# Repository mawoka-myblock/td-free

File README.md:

opencode -s ses_eeea170f0ffeTvjjMf0spo0cMp

# Td-Free

A free and open source device to measure the td value of your filaments.

Documentation: [API.md](API.md) describes the HTTP API, [FIRMWARE.md](FIRMWARE.md) explains how the firmware works.

The CAD is available in the [onshape workspace](https://cad.onshape.com/documents/e7ec65aec40b24c9a33c1902/w/dc90f86d4d08d2181a707cee/e/a86c6c8c0a4124509901ffce)
(licensed under [CC BY-SA 4.0](https://creativecommons.org/licenses/by-sa/4.0/)) and the print files can be downloaded from [Printables](https://www.printables.com/model/919380-td-free)

## Comparison to TD-1 by Ajax

| TD-Free                   | TD-1                                     |
| ------------------------- | ---------------------------------------- |
| **Small**                 | Slightly bigger                          |
| **Cheap**                 | More expensive                           |
| Measures td and color     | **Measures color and td**                |
| WiFi-enabled              | Only via usb and screen                  |
| **Open-Source Code**      | Closed source                            |
| **No license required**   | License needs to be purchased            |
| No integrations available | **Perfectly integrated into HueForge**   |
| **CAD available**         | CAD not available                        |
| only for checking samples | **monitor td of spool as it's printing** |

So, in summary, the Td-Free is **cheaper**, **open-source**, **smaller** and **wifi-enabled**.

## Buy one

**Explore [my online store](https://mawoka.eu/shop) where you can buy the PCB or a fully assembled Td-Free.**

## Make one

### Buy only the PCB

If you got the PCB, just print the parts provided at [Printables](https://www.printables.com/model/919380-td-free-an-open-source-alternative-to-the-td-1).
You have to use black filament for the specifc parts marked as such, but for the others, you can mix and match them! Let's get to the assembly:

1. Insert the LED module into the position in the case at the bottom. Press it down firmly.
2. Insert the two black pieces. The one with the channel first, so that the channel is open to the top. Make sure you see the yellow LED module through the hole in the channel!
3. Now, insert the second black piece with the rectangular cutout as well. Make sure again that the cutout is above the LED hole.
4. Slide the PCb with the USB-C connector in at an angle and make sure it's fully slid in.
5. Push the PCb into place and make sure it is really sitting flat. **Watch out for the LED cable to not get damaged!**
6. Put the lid on
7. Done! Measure your Td!

### From Scratch
Get the PCB from a manufacturer like JLCPCB, PCBway or whatever. Now, you'll also want to get the following components:
- `VEML7700` (TR or TT is only about the packaging, so choose the cheaper one)
- `WS2812B` (In the 5050 variant)
- `ESP32-C3 Supermini` ([Here from AliExpress](https://s.click.aliexpress.com/e/_DmNdnTB))
- `AOSS32334C`
- [This LED module](https://s.click.aliexpress.com/e/_DF3Gdpb) Get the Cold White version

Solder all your parts to the PCB. The LED module cables have to solderd from the bottom and should be around 45mm long.
Now, follow all the steps from above. For flashing, just follow the instructions to get Esp-rs working and run `cargo run --release`.

## Looking for the old README?
Click [here](https://github.com/mawoka-myblock/td-free/blob/v2.0.0/README.md).

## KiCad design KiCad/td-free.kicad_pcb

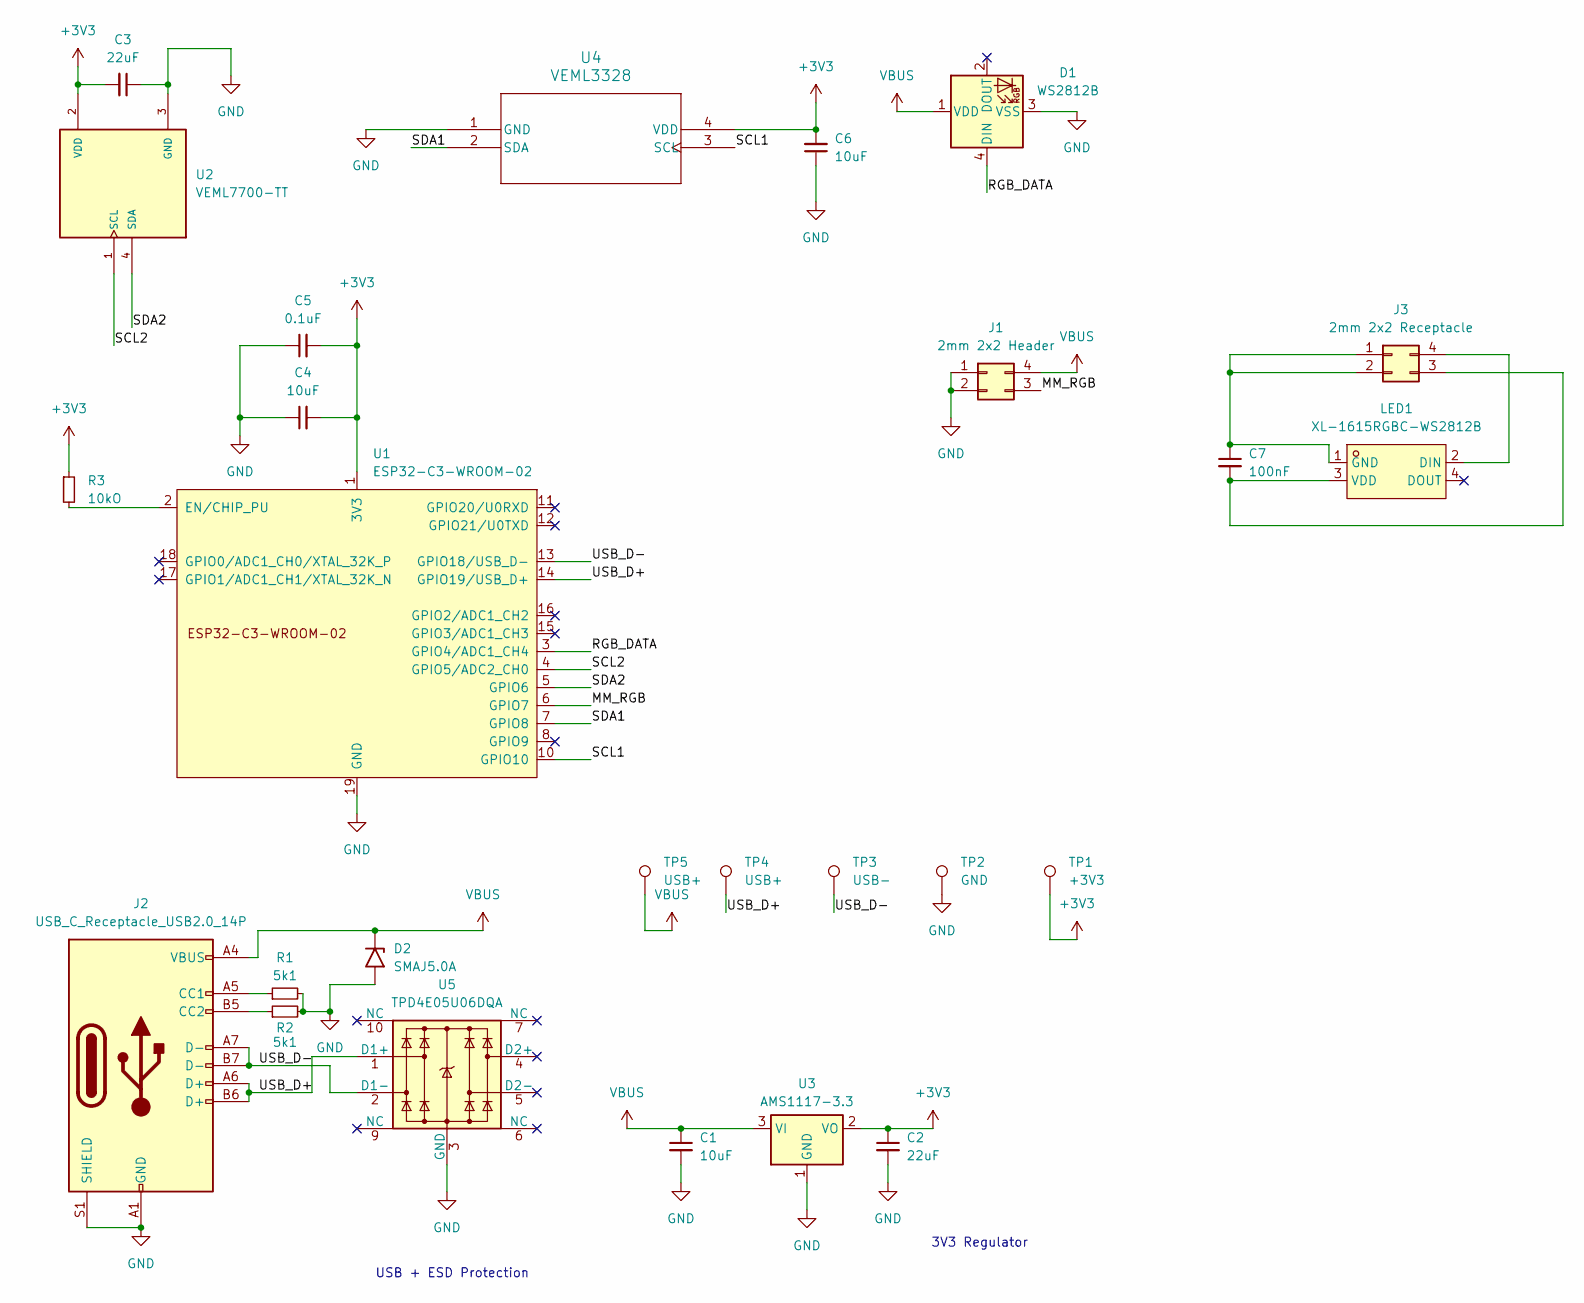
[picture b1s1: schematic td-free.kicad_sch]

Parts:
C1, C4, C6: 10uF; C_0805_2012Metric
C2, C3: 22uF; C_0805_2012Metric
C5: 0.1uF; C_0805_2012Metric
C7: 100nF; C_0805_2012Metric
D1: WS2812B; LED_WS2812B_PLCC4_5.0x5.0mm_P3.2mm
D2: SMAJ5.0A; D_SMA
J1: 2mm 2x2 Header; HDR-SMD_4P-P2.00-V-M-R2-C2-LS6.4-EH
J2: USB_C_Receptacle_USB2.0_14P; USB_C_Receptacle_GCT_USB4105-xx-A_16P_TopMnt_Horizontal
J3: 2mm 2x2 Receptacle; PinHeader_2x02_P2.00mm_Vertical_SMD
LED1: XL-1615RGBC-WS2812B; LED-SMD_4P-L1.6-W1.5_XL-1615RGBC-WS2812B-1; LCSC Part C5349954
R1, R2: 5k1; R_0805_2012Metric_Pad1.20x1.40mm_HandSolder
R3: 10kO; R_0805_2012Metric_Pad1.20x1.40mm_HandSolder
TP1: +3V3; TestPoint_Pad_D1.0mm
TP2: GND; TestPoint_Pad_D1.0mm
TP3: USB-; TestPoint_Pad_D1.0mm
TP4, TP5: USB+; TestPoint_Pad_D1.0mm
U1: ESP32-C3-WROOM-02
U2: VEML7700-TT; XDCR_VEML7700-TT; PARTREV 1.6
U3: AMS1117-3.3; SOT-223-3_TabPin2
U4: VEML3328; SMD_L3328_VIS
U5: TPD4E05U06DQA; USON-10_2.5x1.0mm_P0.5mm

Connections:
+3V3: C2.1, C3.2, C4.2, C5.2, C6.2, R3.1, TP1.1 (1_1), U1.1 (3V3), U2.2 (VDD), U3.2 (VO), U4.4 (VDD)
/MM_RGB: J1.3, U1.6 (GPIO7)
/RGB_DATA: D1.4 (DIN), U1.3 (GPIO4/ADC1_CH4)
/SCL1: U1.10 (GPIO10), U4.3 (SCL)
/SCL2: U1.4 (GPIO5/ADC2_CH0), U2.1 (SCL)
/SDA1: U1.7 (GPIO8), U4.2 (SDA)
/SDA2: U1.5 (GPIO6), U2.4 (SDA)
/USB_D+: J2.A6 (D+), J2.B6 (D+), TP4.1 (1_1), U1.14 (GPIO19/USB_D+), U5.1 (D1+)
/USB_D-: J2.A7 (D-), J2.B7 (D-), TP3.1 (1_1), U1.13 (GPIO18/USB_D-), U5.2 (D1-)
GND: C1.2, C2.2, C3.1, C4.1, C5.1, C6.1, D1.3 (VSS), D2.2 (A2), J1.1, J1.2, J2.A1 (GND), J2.A12 (GND), J2.B1 (GND), J2.B12 (GND), J2.S1 (SHIELD), R1.2, R2.2, TP2.1 (1_1), U1.9 (GND), U1.19 (GND), U2.3 (GND), U3.1 (GND), U4.1 (GND), U5.3 (GND), U5.8 (GND)
unnamed: J2.A5 (CC1), R1.1
unnamed: J2.B5 (CC2), R2.1
unnamed: C7.1, J3.1, J3.2, LED1.1 (GND)
unnamed: C7.2, J3.3, LED1.3 (VDD)
unnamed: J3.4, LED1.2 (DIN)
unnamed: R3.2, U1.2 (EN/CHIP_PU)
VBUS: C1.1, D1.1 (VDD), D2.1 (A1), J1.4, J2.A4 (VBUS), J2.A9 (VBUS), J2.B4 (VBUS), J2.B9 (VBUS), TP5.1 (1_1), U3.3 (VI)

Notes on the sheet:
3V3 Regulator
USB + ESD Protection

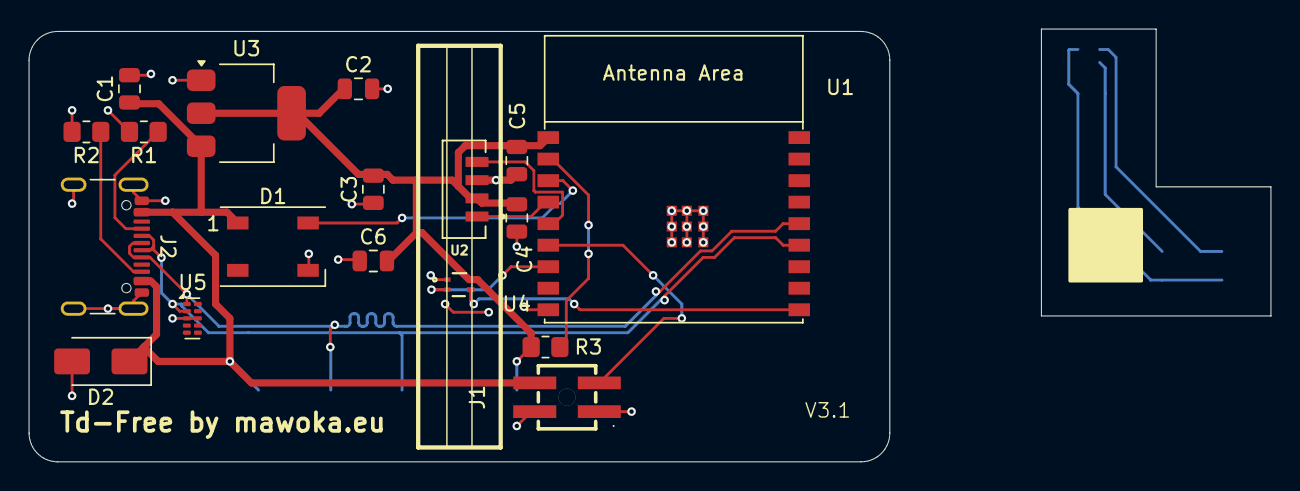
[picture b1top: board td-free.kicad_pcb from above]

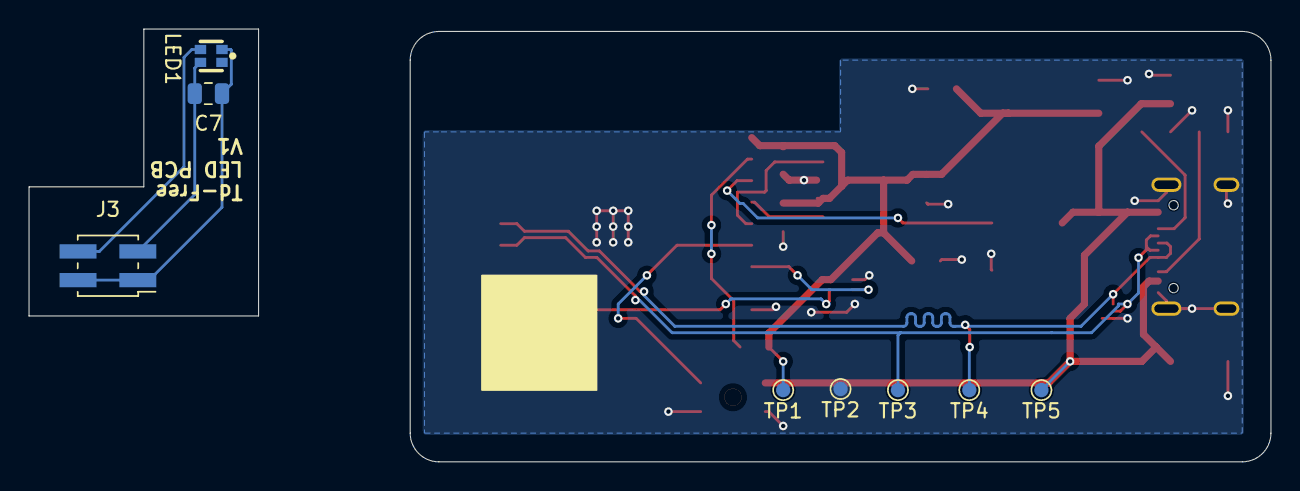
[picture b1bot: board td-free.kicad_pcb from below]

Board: 2 copper layers, 60.0 x 30.0 mm, 28 parts (8 on the bottom side), 17 nets.

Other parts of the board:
B1, B2: Board

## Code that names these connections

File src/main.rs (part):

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        LedcDriver::new(
            peripherals.ledc.channel1,
            light_timer_driver,
            peripherals.pins.gpio7,
        )
        .unwrap(),
    ));
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        LedType::new(peripherals.rmt.channel0, peripherals.pins.gpio21).unwrap(),
    ));
    let ws2812_new: ArcLed = Arc::new(Mutex::new(
        LedType::new(peripherals.rmt.channel1, peripherals.pins.gpio4).unwrap(),
    ));
    ws2812_old
        .lock()
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    let veml_res = esp_idf_svc::hal::task::block_on(initialize_veml(
        Pins {
            i2c: peripherals.i2c0,
            sda1: peripherals.pins.gpio6,
            scl1: peripherals.pins.gpio5,
            sda2: peripherals.pins.gpio8,
            scl2: peripherals.pins.gpio10,
        },
        ws2812_old.clone(),
        ws2812_new.clone(),
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    // --- Serial connection setup ---
    let mut serial_driver = UsbSerialDriver::new(
        peripherals.usb_serial,
        peripherals.pins.gpio18,
        peripherals.pins.gpio19,
        &UsbSerialConfig::new(),
    )
    .unwrap();
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
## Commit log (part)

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2024-06-21 :sparkles: Working version
2024-06-21 :sparkles: Update workflow
2024-06-21 :sparkles: Finalized README.md
2024-07-06 Link to different ESP32-C3
2024-07-16 :sparkles: Create aio build for CI to upload with single file to esp32
2024-07-16 :sparkles: Improved readme
2024-08-09 :bug: Fix prebuilt binary not working
2024-09-07 Update note for V2
2024-10-14 :sparkles: V3 with PCB
2024-10-26 :sparkles: Algorithm adjustments possible
2024-10-26 :sparkles: inital try at release automation
2024-10-26 :sparkles: CI Update 1
2024-10-26 :sparkles: CI Update 2
2024-10-26 :sparkles: CI Update 3
2024-10-26 :sparkles: CI Update 4
2024-10-26 :sparkles: CI Update 5
2024-10-26 :sparkles: CI Update 6
2024-10-26 :sparkles: CI Update 7
2024-10-26 Add V1.2 PCB without wrong condensator
2024-10-26 Add more specific note on parts for self-sourcing
2024-10-26 Optimize trace on PCB
2024-10-26 Fix typo in README
2024-11-06 Create LICENSE
2024-12-20 :sparkles: Allow comma digit input for algorithm page
2024-12-20 :bug: Pin rust toolchain for github action
2024-12-21 :bug: Fix build issues
2024-12-30 Init mdns
2025-01-16 :sparkles: Version injection on website
2025-01-31 :sparkles: Handlers split into separate file
2025-01-31 :sparkles: Improved error handling
2025-02-01 :wip: Progress
2025-02-01 :bug: Fix build script
2025-02-01 :wip: basic changes
2025-02-01 :wip: Edge-Http test
2025-02-01 :wip: Compiling but panicking
2025-02-02 :wip: Changes
2025-02-02 Make the WS thing run
2025-02-03 :wip: Basics working with edge-http
2025-02-03 :wip: Basics working formatted
2025-02-03 :sparkles: Better WebSocket now working
2025-02-03 :sparkles: Final refactoring finished
2025-02-04 :sparkles: Fix GitHub Actions Release Build
2025-02-04 :bug: CI fix
2025-02-04 Fix GitHub Actions build again
2025-02-08 :sparkles: Working serial connection
2025-02-10 :sparkles: Averaged reading progress
2025-02-10 :bug: Fix release build file
2025-02-13 Quick save
2025-02-23 :sparkles: Averaged data working
2025-02-23 :bug: Fix release workflow
2025-02-23 :bug: Add small delay on page load before connecting to websocket
2025-03-09 :sparkles: First Prototype for improved PCB
2025-03-09 :sparkles: Even better fallback handling
2025-03-09 :sparkles: Adjustable threshold
2025-03-09 :bug: Fix formatting in algorithm page
2025-03-15 :sparkles: First test with new PCB
2025-03-28 :sparkles: PCB Progress
2025-03-28 :sparkles: Further USB support progress
2025-03-29 :sparkles: Basic Spoolman Integration working
2025-03-29 Renamed Algorithm page to settings page
2025-03-29 :sparkles: New Workflow for building firmware
2025-03-29 :bug: Fix Build Workflow (1)
2025-03-29 :bug: Fix Build Workflow (2)
2025-03-29 :bug: Fix Build Workflow (3)
2025-03-29 :bug: Fix Build Workflow (4)
2025-03-29 :bug: Fix Build Workflow (5)
2025-03-29 :bug: Fix Build Workflow (6)
2025-03-29 Fix Workflow (7)
2025-03-29 Fix Workflow
2025-04-12 :sparkles: New PCB working, software backwards compatible
2025-04-17 :bug: Adjust to also allow HF in Serial Connection
2025-04-17 Add Workflow
2025-04-23 :sparkles: HueForge communication working
2025-04-23 :sparkles: Improved USB performance drastically
2025-04-27 :bug: Sending TD data to HueForge with only one digit precision
2025-05-05 Add serial barcode to PCB
2025-05-05 Make spoolman field customizable
2025-05-21 Make fallback mode only
2025-06-07 Added median and outlier filtering to the code and slightly increased the sample count
2025-06-11 Added median to baseline readings
2025-06-26 enabled debug logging for now
2025-06-27 working on the veml3328
2025-06-27 sensor ALMOST works. Bit banging allows the correct values, only need to do calibration and correct display
2025-06-27 whitebalance correction
2025-06-27 running median buffer, wifi retry and some color calibration
2025-06-27 Sensor initial tests, baseline rgb reading at 25%
2025-06-27 75 brightness works a bit better
2025-06-28 calibration is still not quite right
2025-06-28 calibration help
2025-06-28 custom calibration and TD adjustment still needs work
2025-06-28 calibration
2025-06-28 calibration, slider changes, nvs key bug fix
2025-06-28 html update
2025-07-06 reworked wifi a bit to keep the connection alive in the background. Work on color calibration and trying to always use 100% led during measuring to reduce measuring noise.
2025-07-06 removed the websocket connection. It broke frequently and the fallback polling method is simple and robust.
2025-07-06 removed obsolete average code and fixed td calculation
2025-07-06 calibration now finally works correctly. Still need to calculate the correct value for the automatic brightness adjustment. Also, we currently keep the led at 100% all the time, which helps in reduci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
2025-07-06 Forgot to set the new calibration TD.
2025-07-06 The color calibration and values now finally work correctly. Currently, there is still a small discrepancy under a td of 2.0 that gets bigger as we get near zero. I'll probably have to find a good va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
2025-07-11 reduced std to smaller value to not trigger warning if the result is still correct.
2025-07-11 just some cleanup
2025-07-12 wifi is now it's own thread. index.html has now a custom color picker. Calibration block is collapsable.
2025-07-12 readded hueforge connection. This currently does not work for me, but I would guess that this is a linux hueforge problem.
2025-07-12 Linter cleanup
2025-07-12 Base Cleanup
2025-07-13 Big refactoring
2025-07-13 Better visual feedback on algorithm page
2025-07-13 Pin espflash and update CI toolchain
2025-07-14 Basic main optional rgb sensor
2025-07-14 Optional RGB sensor
2025-07-23 Add timeout to requests
2025-08-08 :sparkles: Disable logs by default
2025-08-08 :bug: Fix build.yml
2025-08-08 Restore HueForge connectivity
2025-08-10 :bug: Fix debug build
2025-08-10 :bug: Fix release build script
2025-08-12 Update dependencies
2025-08-12 Progress
2025-10-18 Improvements with Async and fixes with buffers not being passed around correctly
2025-11-16 Basic bluetooth
2025-11-16 quicksave
2025-11-16 Bluetooth kinda working
2025-11-16 Fix sdkconfig
2025-11-19 Add version command, settings and other fixes
2025-11-30 :sparkles: Working calibration
2025-12-26 Maybe fix main page not loading
2025-12-26 Fix LED dimming down after measurement
2026-04-08 Add Cargo.toml
2026-04-08 Improve td reading accuracy
2026-04-08 :arrow_up: Bump time from 0.3.41 to 0.3.47
    Bumps [time](https://github.com/time-rs/time) from 0.3.41 to 0.3.47.
    - [Release notes](https://github.com/time-rs/time/releases)
    - [Changelog](https://github.com/time-rs/time/blob/main/CHANGELOG.md)
    - [Commits](https://github.com/time-rs/time/compare/v0.3.41...v0.3.47)
    ---
    updated-dependencies:
2026-04-08 Fix workflow and rust cache
2026-06-11 :sparkles: Progress
2026-06-12 Basics working
2026-06-12 Set correct toolchains
2026-06-12 Fix workflow uploading to correct bucket
2026-06-12 Call enable on sensor init
2026-06-13 Most features mostly reimplemted
2026-06-13 Clippy warnings
2026-06-13 Add commit for git dependencies
2026-06-13 Fix typo in logging
2026-06-13 Add more padding in time after led brightness change
2026-06-14 Add LED indication
2026-06-14 Add debug build
2026-06-14 Add HueForge compatibility back
2026-06-14 Fix clippy warnings
2026-06-14 Fix build workflow
2026-06-14 Fix workflow to upload both artifacts
2026-06-14 Update used workflows
2026-06-14 Disable unneeded features in dependencies
2026-06-25 Add untested multi consumer structure
2026-06-25 Fix release workflow
